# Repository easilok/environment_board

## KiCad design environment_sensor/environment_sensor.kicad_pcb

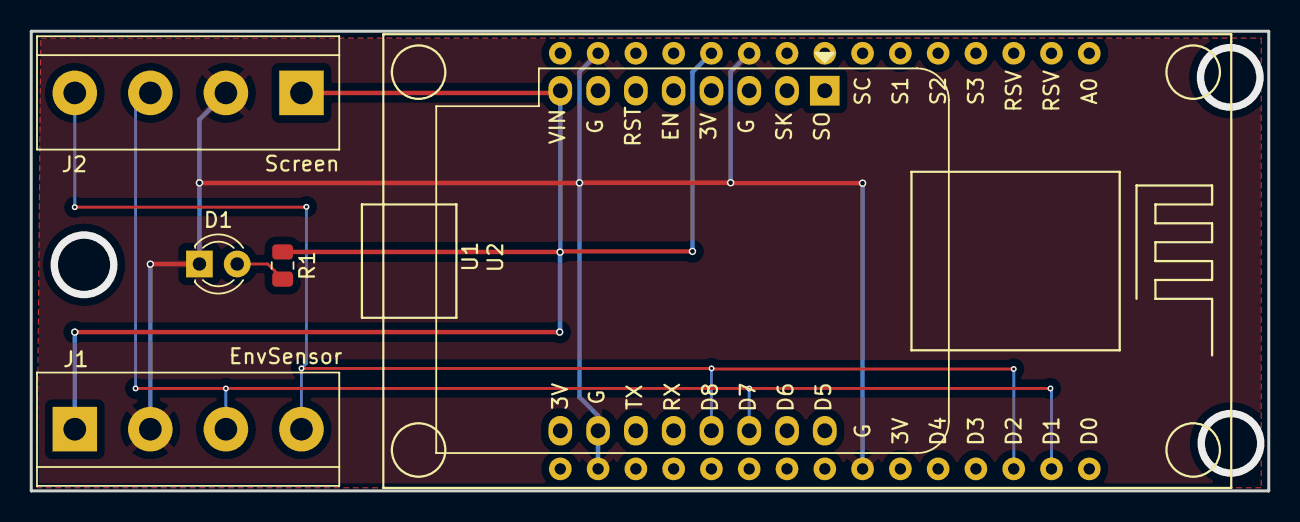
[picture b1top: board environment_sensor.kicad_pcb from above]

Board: 2 copper layers, 83.2 x 30.9 mm, 6 parts (0 on the bottom side), 5 nets.

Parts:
D1: LED; LED_D3.0mm
J1: EnvSensor; TerminalBlock_bornier-4_P5.08mm
J2: Screen; TerminalBlock_bornier-4_P5.08mm
R1: 10K; R_0805_2012Metric
U1: WeMos_D1_mini; WEMOS_D1_mini_light
U2: NodeMCU_ESP12E; NodeMCU1.0_12-E

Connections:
/+3V3: J1.1, J2.1, R1.1, U1.8 (3V3), U2.11 (3V3)
/I2C_SCL: J1.3, J2.3, U1.14 (SCL/D1), U2.29 (D1)
/I2C_SDA: J1.4, J2.4, U1.13 (SDA/D2), U2.28 (D2)
GND: D1.1 (K), J1.2, J2.2, U1.10 (GND), U2.10 (GND), U2.14 (GND), U2.17 (GND), U2.24 (GND)
unnamed: D1.2 (A), R1.2

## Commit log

2022-04-29 First version sent to production
